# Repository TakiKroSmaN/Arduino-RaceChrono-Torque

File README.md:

# Arduino-Race-Chrono-Torque
Rece Chrono or Torque for cars without OBD II

This is my datalogger for car without OBD II in my case Honda Civic B16A2
You can connect with RaceChrono or Torque application using a buetooth HC-05 or HC-06.
I used Arduino Pro Micro.
In RaceChrono there is no, or I don't know how to create new sensor so I used water temp as gear pos and intake temp as VTEC indicator etc.
In Torque it's shows under correct names.
Base for Torque I have found here: https://torque-bhp.com/wiki/Arduino

there are some bugs for sure but in my car is working good enoght

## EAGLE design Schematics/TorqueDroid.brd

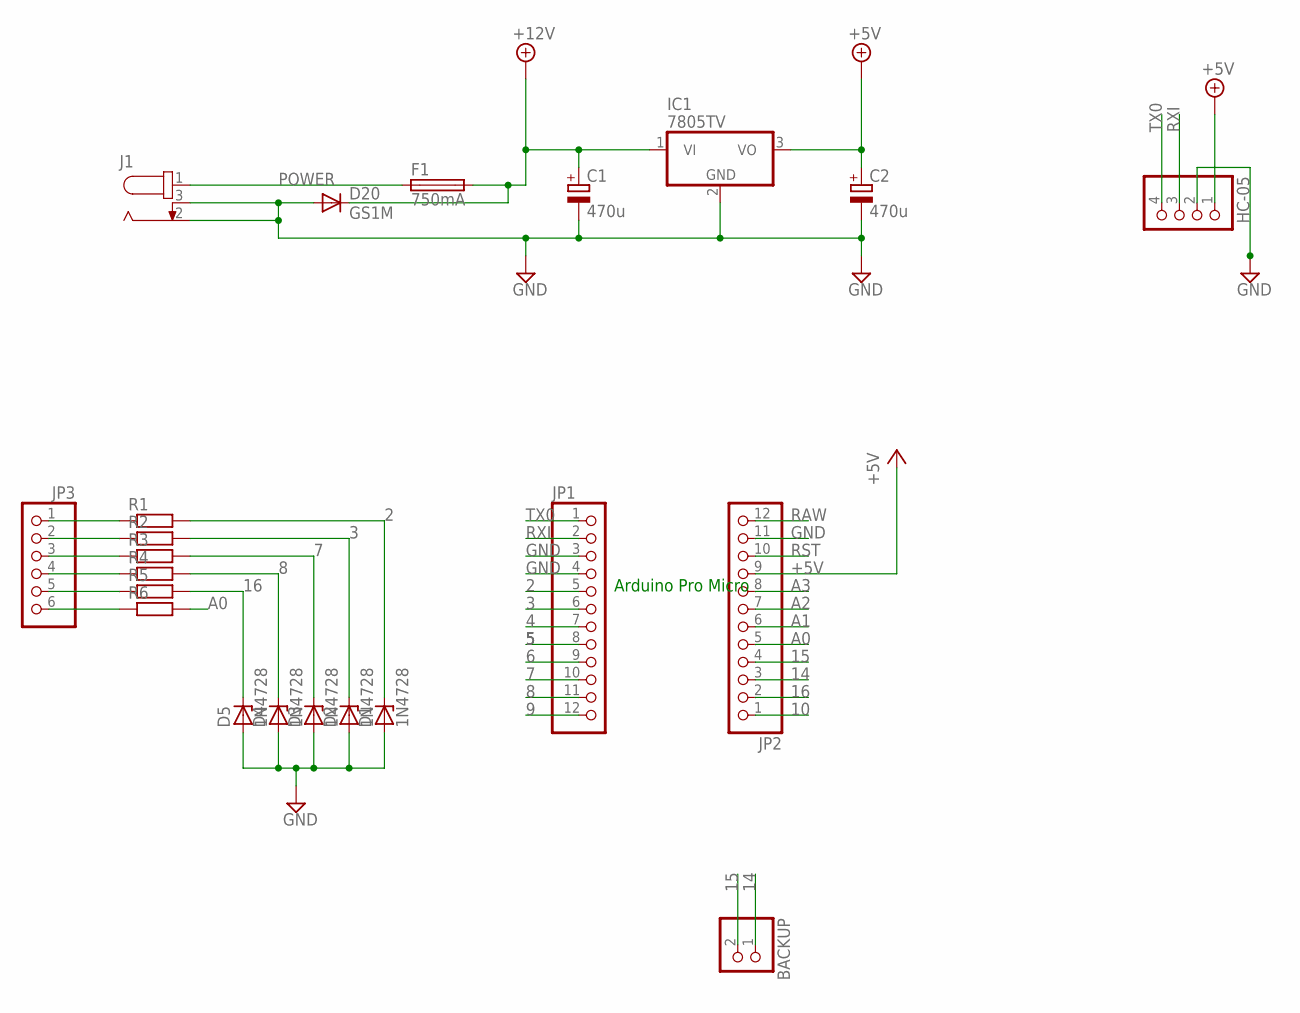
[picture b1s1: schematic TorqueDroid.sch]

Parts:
BACKUP: PINHD-1X2; 1X02
C1, C2: 470u; E3,5-10
D1, D2, D3, D4, D5: 1N4728; DO41Z10
D20: GS1M; SMA
F1: 750mA; MF-SMDF050
HC-05: PINHD-1X4; 1X04
IC1: 7805TV; TO220V
J1: 694102303002; 69410X303002
JP1, JP2: PINHD-1X12; 1X12
JP3: PINHD-1X6/90; 1X06/90
R1, R2, R3, R4, R5, R6: R-EU_R0805; R0805

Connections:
2: D1.C, JP1.5, R1.2
3: D2.C, JP1.6, R2.2
4: JP1.7
5: JP1.8
6: JP1.9
7: D3.C, JP1.10, R3.2
8: D4.C, JP1.11, R4.2
9: JP1.12
10: JP2.1
14: BACKUP.1, JP2.3; also elsewhere on the board
15: BACKUP.2, JP2.4; also elsewhere on the board
16: D5.C, JP2.2, R5.2
+5V: C2.+, HC-05.1, IC1.3 (VO), JP2.9; also elsewhere on the board
+9V: C1.+, D20.C, F1.2, IC1.1 (VI)
A0: JP2.5, R6.2
A1: JP2.6
A2: JP2.7
A3: JP2.8
GND: C1.-, C2.-, D1.A, D2.A, D3.A, D4.A, D5.A, D20.A, HC-05.2, IC1.2 (GND), J1.2, J1.3, JP1.3, JP1.4, JP2.11; also elsewhere on the board
unnamed: JP3.1, R1.1
unnamed: JP3.2, R2.1
unnamed: JP3.3, R3.1
unnamed: JP3.4, R4.1
unnamed: JP3.5, R5.1
unnamed: JP3.6, R6.1
POWER: F1.1, J1.1
RAW: JP2.12
RST: JP2.10
RXI: HC-05.3, JP1.2; also elsewhere on the board
TX0: HC-05.4, JP1.1; also elsewhere on the board

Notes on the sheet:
Arduino Pro Micro

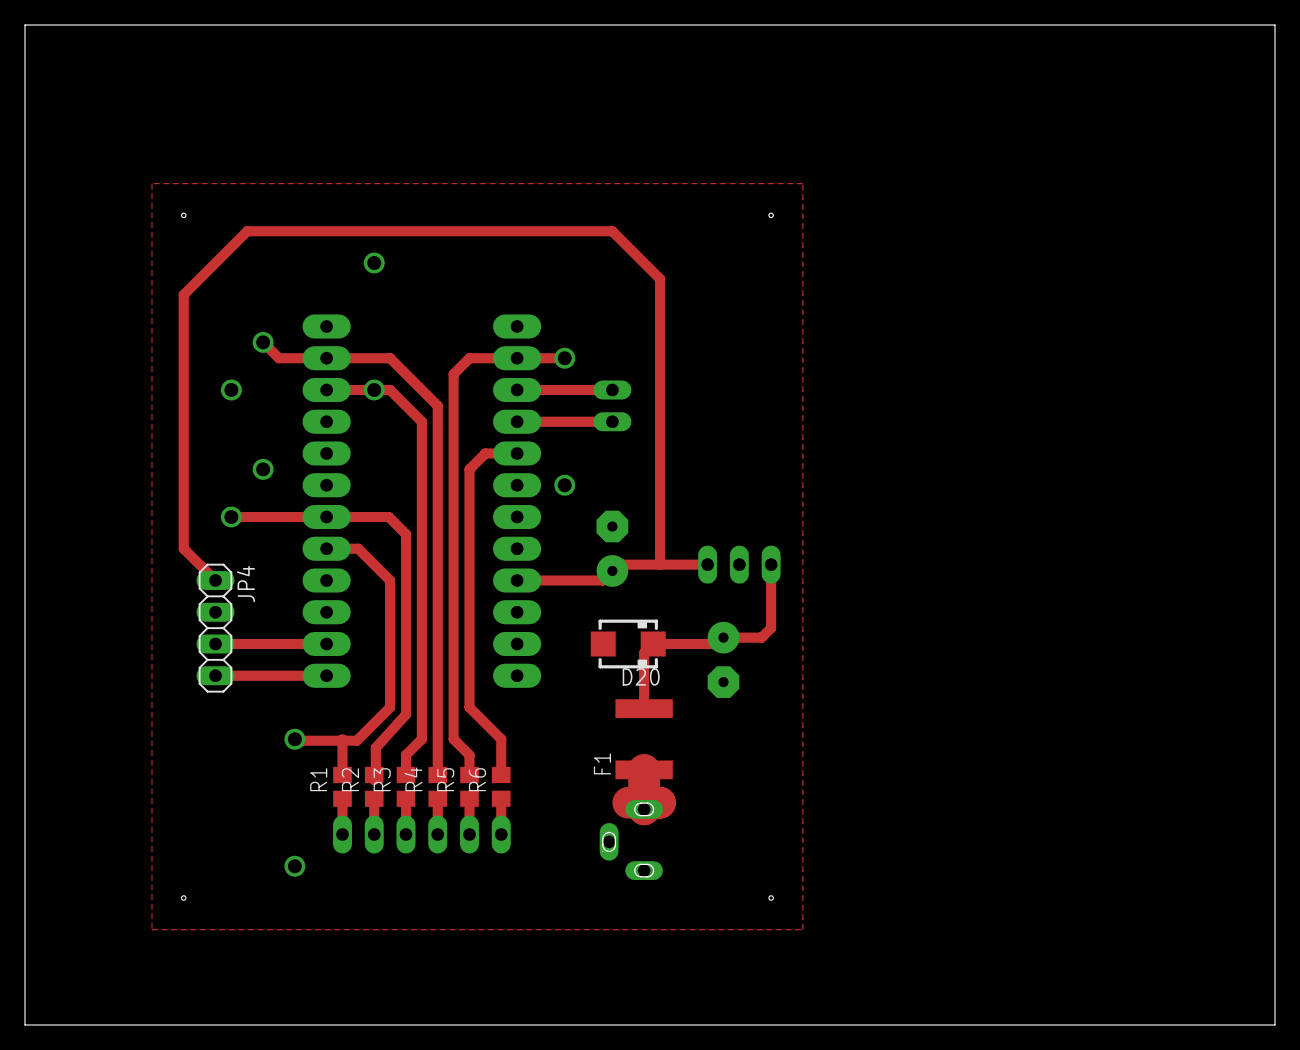
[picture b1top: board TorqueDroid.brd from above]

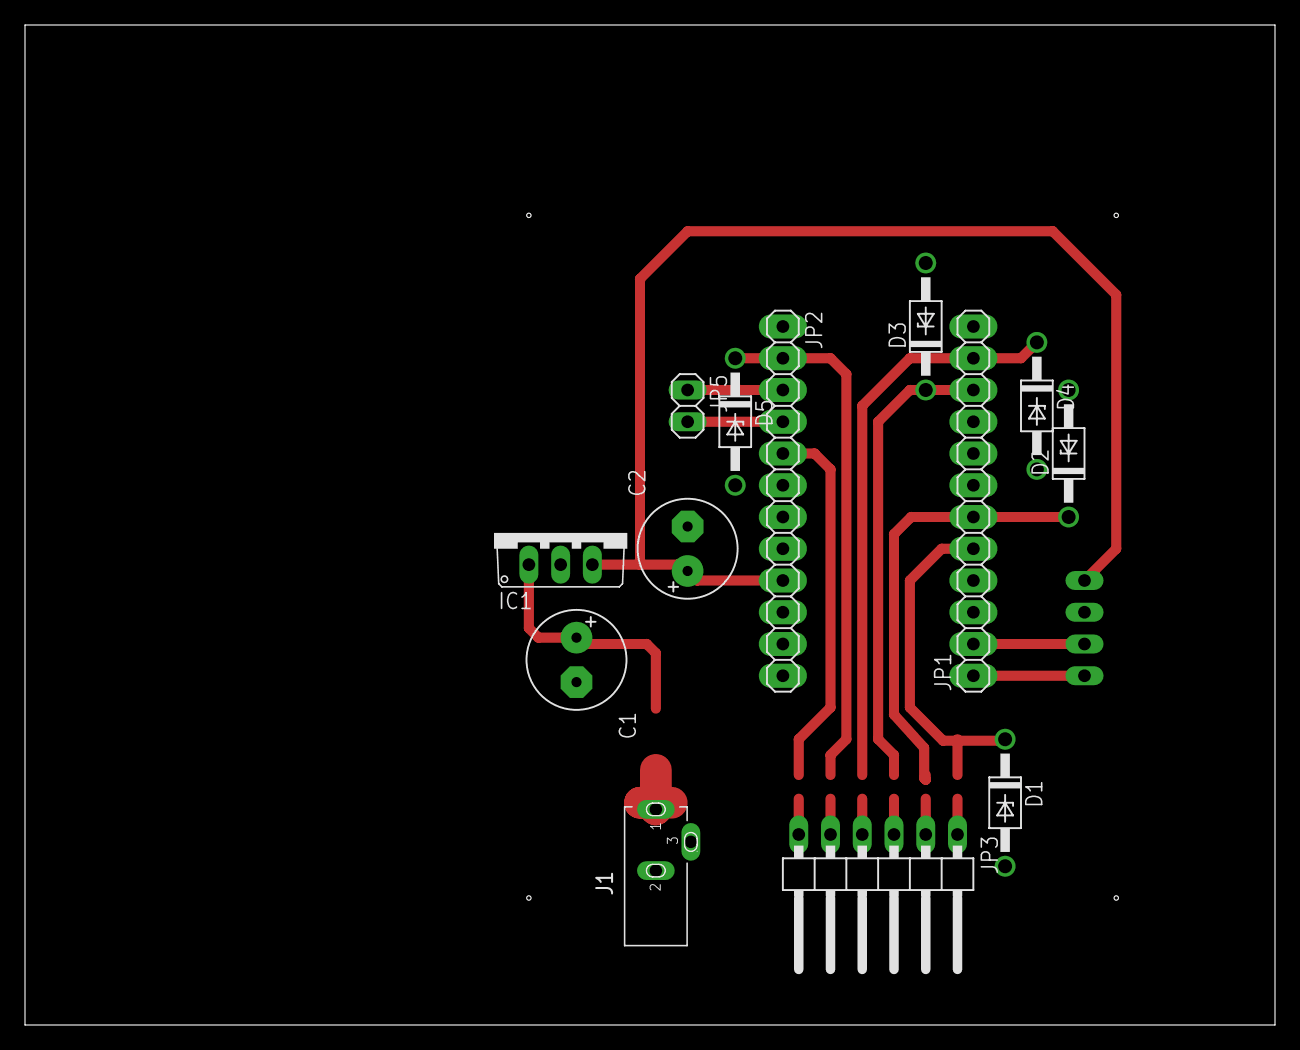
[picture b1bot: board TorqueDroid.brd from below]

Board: 2 copper layers, 99.9 x 79.9 mm, 22 parts (13 on the bottom side), 20 nets.

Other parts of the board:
JP4: 1X04
JP5: 1X02

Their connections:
14: JP5.1; also elsewhere on the board
15: JP5.2; also elsewhere on the board
+5V: JP4.1; also elsewhere on the board
GND: JP4.2; also elsewhere on the board
RXI: JP4.3; also elsewhere on the board
TX0: JP4.4; also elsewhere on the board

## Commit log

2018-03-31 Arduino RaceChrono & Torque
    This is my datalogger for car without OBD II in my case Honda Civic B16A2
    You can connect with RaceChrono or Torque application using a buetooth HC-05 or HC-06.
    In RaceChrono there is no, or I don't know how to create new sensor so I used water temp as gear pos and intake temp as VTEC indicator etc.
    In Torque it's shows under correct names.
    Base for Torque I have found here: https://torque-bhp.com/wiki/Arduino
    there are some bugs for sure but in my car is working good enoght

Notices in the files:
parts and their libraries:
Wurth_Elektronik_Electromechanic_DC_Powe: Copyright: Würth Elektronik
